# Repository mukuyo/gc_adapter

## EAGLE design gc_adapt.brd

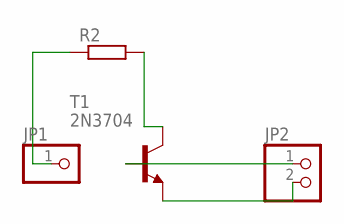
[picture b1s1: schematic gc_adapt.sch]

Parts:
JP1: PINHD-1X1; 1X01
JP2: PINHD-1X2; 1X02
R2: R-EU_0204/5; 0204/5
T1: 2N3704; TO92

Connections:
unnamed: JP2.1, T1.1 (B)
unnamed: JP2.2, T1.3 (E)
unnamed: R2.2, T1.2 (C)
unnamed: JP1.1, R2.1

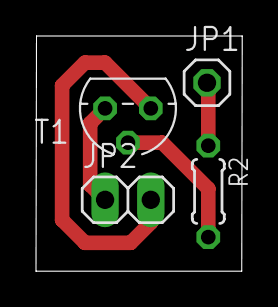
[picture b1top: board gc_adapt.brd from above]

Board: 2 copper layers, 11.5 x 13.1 mm, 4 parts (0 on the bottom side), 4 nets.

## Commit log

2023-04-18 change directory
